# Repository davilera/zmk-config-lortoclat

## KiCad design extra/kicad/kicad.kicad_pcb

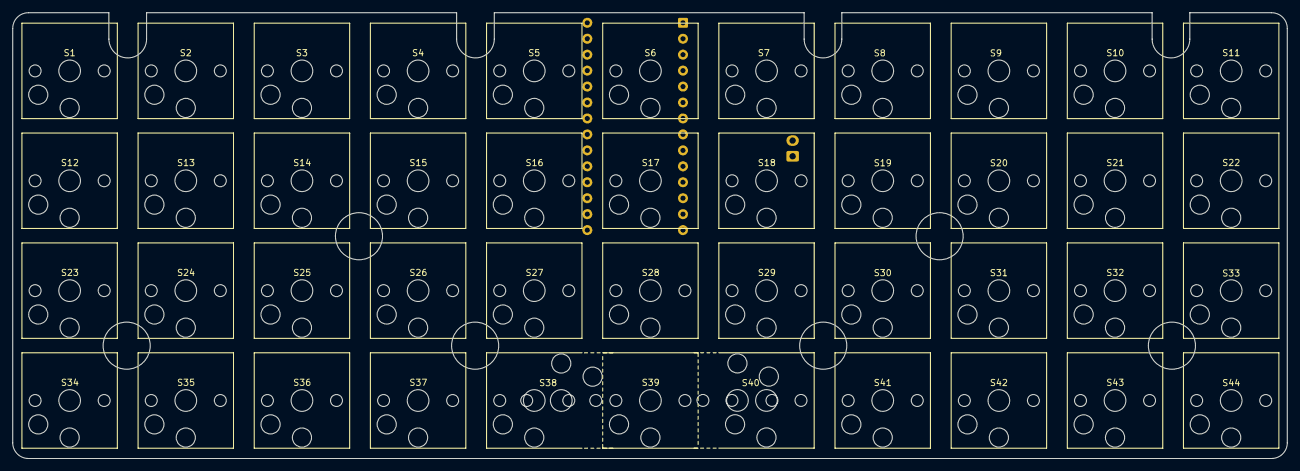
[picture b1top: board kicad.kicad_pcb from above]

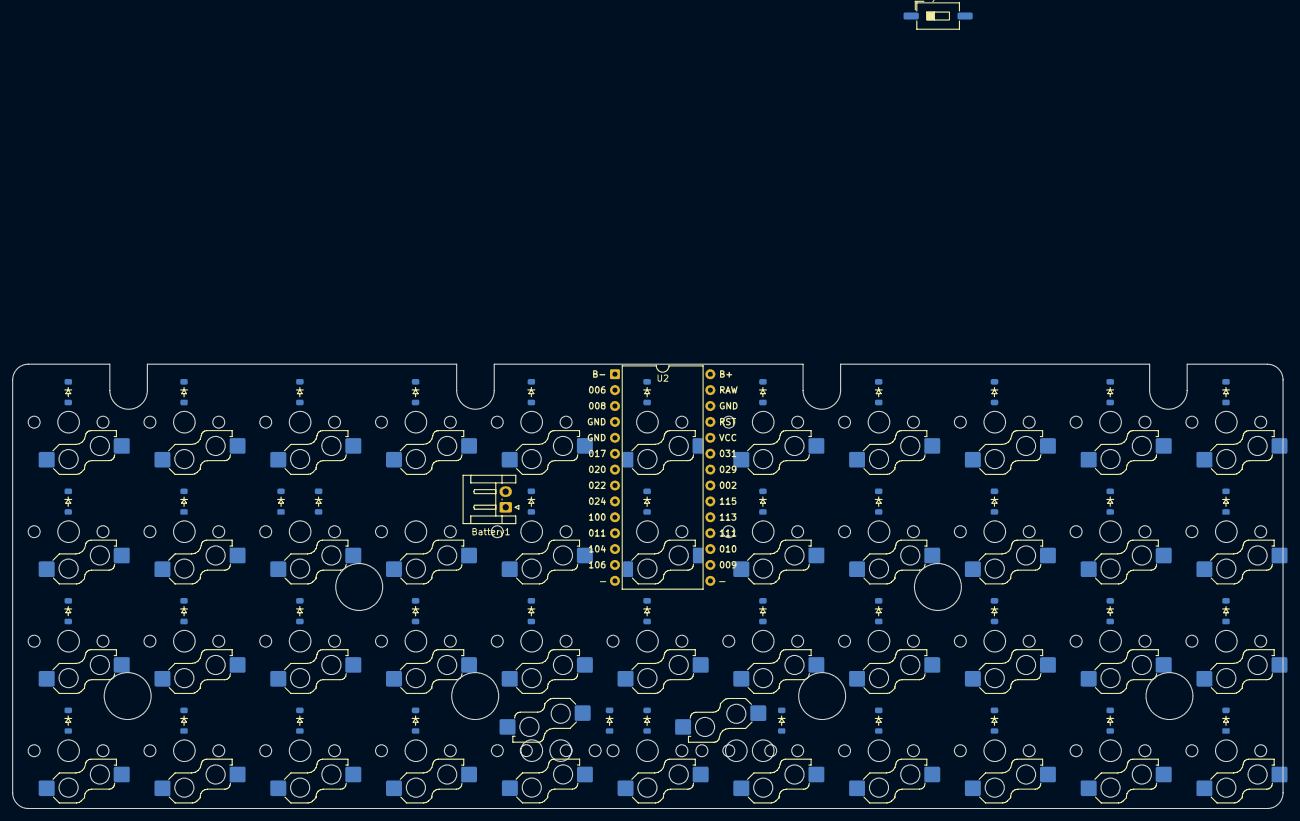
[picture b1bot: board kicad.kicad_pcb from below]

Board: 2 copper layers, 203.0 x 71.0 mm, 93 parts (47 on the bottom side), 62 nets, no tracks yet.

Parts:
Battery1: Battery_Cell; JST_EH_S2B-EH_1x02_P2.50mm_Horizontal
BatterySwitch1: Switch; SW_DIP_SPSTx01_Slide_6.7x4.1mm_W8.61mm_P2.54mm_LowProfile
D1, D2, D3, D4, D5, D6, D7, D8, D9, D10, D11, D12, D13, D14, D15, D16, D17, D18, D19, D20, D21, D22, D23, D24, D25, D26, D27, D28, D29, D30, D31, D32, D33, D34, D35, D36, D37, D38, D39, D40, D41, D42, D43, D44: Diode_SOD-123
S1, S2, S3, S4, S5, S6, S7, S8, S9, S10, S11, S12, S13, S14, S15, S16, S17, S18, S19, S20, S21, S22, S23, S24, S25, S26, S27, S28, S29, S30, S31, S32, S33, S34, S35, S36, S37, S38, S39, S40, S41, S42, S43, S44, S45, S46: Hotswap_Choc_V1
U2: MW-R-DP-W; DIP-28_W15.24mm

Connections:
B+: Battery1.1 (+), U2.28 (VCC)
B-: BatterySwitch1.2, U2.1 (GND), U2.14 (GND)
Column 0: S1.1, S12.1, S23.1, S34.1, U2.22 (ADC1/AI1)
Column 1: S2.1, S13.1, S24.1, S35.1, U2.21 (~RESET)
Column 2: S3.1, S14.1, S25.1, S36.1, U2.20 (DIO17/BPS)
Column 3: S4.1, S15.1, S26.1, S37.1, U2.19 (DIO15/SDA)
Column 4: S5.1, S16.1, S27.1, S38.1, S45.1, U2.18 (DIO16/DI4)
Column 5: S6.1, S17.1, S28.1, S39.1, U2.16 (DIO13/DI2)
Column 6: S7.1, S18.1, S29.1, S40.1, S46.1, U2.13 (DIO10/M1)
Column 7: S8.1, S19.1, S30.1, S41.1, U2.12 (DIO9/DO4)
Column 8: S9.1, S20.1, S31.1, S42.1, U2.11 (DIO8/PWM4)
Column 9: S10.1, S21.1, S32.1, S43.1, U2.10 (DIO6/TX)
Column 10: S11.1, S22.1, S33.1, S44.1, U2.9 (DIO4/DO3)
unnamed: Battery1.2 (-), BatterySwitch1.1
unnamed: D1.2 (A), S1.2
unnamed: D2.2 (A), S2.2
unnamed: D3.2 (A), S3.2
unnamed: D4.2 (A), S4.2
unnamed: D5.2 (A), S5.2
unnamed: D6.2 (A), S6.2
unnamed: D7.2 (A), S7.2
unnamed: D8.2 (A), S8.2
unnamed: D9.2 (A), S9.2
unnamed: D10.2 (A), S10.2
unnamed: D11.2 (A), S11.2
unnamed: D12.2 (A), S12.2
unnamed: D13.2 (A), S13.2
unnamed: D14.2 (A), S14.2
unnamed: D15.2 (A), S15.2
unnamed: D16.2 (A), S16.2
unnamed: D17.2 (A), S17.2
unnamed: D18.2 (A), S18.2
unnamed: D19.2 (A), S19.2
unnamed: D20.2 (A), S20.2
unnamed: D21.2 (A), S21.2
unnamed: D22.2 (A), S22.2
unnamed: D23.2 (A), S23.2
unnamed: D24.2 (A), S24.2
unnamed: D25.2 (A), S25.2
unnamed: D26.2 (A), S26.2
unnamed: D27.2 (A), S27.2
unnamed: D28.2 (A), S28.2
unnamed: D29.2 (A), S29.2
unnamed: D30.2 (A), S30.2
unnamed: D31.2 (A), S31.2
unnamed: D32.2 (A), S32.2
unnamed: D33.2 (A), S33.2
unnamed: D34.2 (A), S34.2
unnamed: D35.2 (A), S35.2
unnamed: D36.2 (A), S36.2
unnamed: D37.2 (A), S37.2
unnamed: D38.2 (A), S38.2, S45.2
unnamed: D39.2 (A), S39.2
unnamed: D40.2 (A), S40.2, S46.2
unnamed: D41.2 (A), S41.2
unnamed: D42.2 (A), S42.2
unnamed: D43.2 (A), S43.2
unnamed: D44.2 (A), S44.2
Row 0: D1.1 (K), D2.1 (K), D3.1 (K), D4.1 (K), D5.1 (K), D6.1 (K), D7.1 (K), D8.1 (K), D9.1 (K), D10.1 (K), D11.1 (K), U2.2 (DIO14/SCL)
Row 1: D12.1 (K), D13.1 (K), D14.1 (K), D15.1 (K), D16.1 (K), D17.1 (K), D18.1 (K), D19.1 (K), D20.1 (K), D21.1 (K), D22.1 (K), U2.3 (DIO7/RX)
Row 2: D23.1 (K), D24.1 (K), D25.1 (K), D26.1 (K), D27.1 (K), D28.1 (K), D29.1 (K), D30.1 (K), D31.1 (K), D32.1 (K), D33.1 (K), U2.6 (DO0/PWM2)
Row 3: D34.1 (K), D35.1 (K), D36.1 (K), D37.1 (K), D38.1 (K), D39.1 (K), D40.1 (K), D41.1 (K), D42.1 (K), D43.1 (K), D44.1 (K), U2.7 (DO1/PWM3)

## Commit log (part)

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2024-08-25 Initial User Config.
2024-08-25 Rename files
2024-08-25 Add shield
2024-08-25 Use proper files in shield
2024-08-25 Import keymap from Ben Vallack
2024-08-29 Format overlay
2024-09-01 Add empty readme file
2024-09-01 Add Shell 3D model(s)
2024-09-01 Add Lid 3D model(s)
2024-09-01 Remove Blender backup file
2024-09-01 Add Cover 3D model(s)
2024-09-10 Add Hood 3D model(s)
2024-09-10 Improve Shell 3D model(s)
2024-09-12 Add PCB 3D model(s)
2024-09-18 Update Cover 3D model(s)
2024-09-18 Update pins
2024-09-18 Add test layer
2024-09-18 Fix test layer
2024-09-18 Remove test layer
2024-09-19 Enable BT
2024-09-19 Fix a few names
2024-09-19 Testing BT and thumbs
2024-09-19 Fix layer switch
2024-09-23 Update models to use horizontal thumb keys
2024-09-23 --amend
2024-09-25 Fix cover model
2024-09-25 Test hold-tap
2024-09-25 Fix layers
2024-09-25 Add hold-tap
2024-09-25 Remove unicode and use modifier instead
2024-09-26 Test i18n characters with macros
2024-09-26 Add missing colons
2024-09-26 Fix macro
2024-09-26 Remove invalid include
2024-09-26 Fix typo
2024-09-26 Fix macro definition
2024-09-26 Tweak macro
2024-09-26 Tweak hold tap to accept macro
2024-09-26 Tweak macro speed
2024-09-27 Extract macros into their own file
2024-09-27 Add multiple macros
2024-09-27 Add missing key
2024-09-27 Fixing macros
2024-09-27 Try to fix macros
2024-09-27 Undo macros
2024-09-27 Add macros
2024-09-27 Fix macro name
2024-09-27 Fix two macros
2024-09-29 Define layouts
2024-09-29 Remove invalid keycode
2024-09-29 Fix shift code
2024-09-29 Remove all layers to find error
2024-09-29 Add i18n
2024-09-29 Add sym1
2024-09-29 Add sym2
2024-09-29 Add sys
2024-09-29 Add num
2024-09-29 Add BT
2024-09-29 Use appropriate event for BT codes
2024-09-29 Fix BT
2024-09-29 Swap two keys
2024-09-29 Change space to send dot on double-tap
2024-09-29 Reverse behavior
2024-09-29 Tweak tapping term in space
2024-09-29 Add num/rpt key
2024-09-29 Fix num/rpt key
2024-09-29 Add more i18n chars
2024-09-29 Complete i18n layer
2024-09-30 Add ß
2024-09-30 Add more keys
2024-09-30 Fix duplicated name
2024-09-30 Duplicate sym layer
2024-09-30 Debug layers
2024-09-30 Enable i18n layer
2024-09-30 Enable sym1 layer
2024-09-30 Enable sym2 layer
2024-09-30 Fix sym2 layer
2024-09-30 Enable sys layer
2024-09-30 Fix num layer
2024-09-30 Enable BT layer
2024-09-30 Fix shift in i18n
2024-10-01 Fix guillemots
2024-10-01 Swap CTRL and ALT keys plus minor improvements
2024-10-01 Relocate some combos to alpha 1
2024-10-01 Swap two num keys
2024-10-01 Use numpad numbers in num layer
2024-10-02 Tweak a few keys
2024-10-09 Make alpha2 and i18n layers sticky
2024-10-09 Tweak sticky key behavior
2024-10-09 Tweak sl instead of sk behavior
2024-10-25 Remap a few keys
2024-10-25 Improve hold tap
2024-10-25 Improve hold tap in right thumbs
2024-10-28 Fix duplicate node name
2024-10-29 Move a few more keys around
2024-10-30 Fix a few keys
2024-11-02 Rename keyboard
2024-11-02 Add KLE json file
2024-11-02 Fix KLE JSON
2024-11-02 Fix keyboard JSON
2024-11-02 Remove key
2024-11-02 Simplify layout
2024-11-02 Fix typos and bugs
2024-11-02 Fix wide key position
2024-11-02 Fix JSON
2024-11-02 Fix keymap
2024-11-02 Add layers
2024-11-02 Set all keys in all secondary layers to none
2024-11-02 Add missing keys in alpha layer
2024-11-02 Add layer switches and a few more keys
2024-11-02 Add i18n keys without macros
2024-11-02 Add missing i18n keys
2024-11-03 Add test macro
2024-11-03 Add i18n macros into i18n layer
2024-11-03 Add sym layer
2024-11-03 Add num layer
2024-11-03 Add sys layer
2024-11-24 Add keyboard model
2024-11-26 Fix models
2024-12-19 Update 3d models
2024-12-23 Update config files
2024-12-23 Update JSON
2024-12-23 Add missing keys in keymap
2024-12-23 Test layout
2024-12-28 Fix some i18n keys
2024-12-28 Tweak more keys
2024-12-28 Tweak fn keys
2024-12-29 Add MO keys
2024-12-29 Add "I" macros
2024-12-29 Tweak shift/caps behavior
2024-12-30 Add qwerty
2024-12-30 Reorder mod keys
2024-12-30 Add symbol tweak on qwerty
2024-12-30 Tweak conditional layers
2024-12-30 Add access to num layer
2024-12-30 Add ctrl nums
2024-12-31 Add shifts as modtaps
2024-12-31 Fix keys in qwerty i18n
2024-12-31 Change mod row
2024-12-31 Add number row as hold keys
2024-12-31 Fix shift
2024-12-31 Add num row in qwerty
2024-12-31 Tweak combo
2025-01-03 Fix qwerty num layout
2025-01-08 Swap LALT and LGUI keys
2025-01-09 Move sym keys one position outwards
2025-01-09 Tweak arrows in sym layer
2025-01-10 Swap M and D
2025-01-10 Move some keys around
2025-01-10 Add ndash and mdash characters
2025-01-10 Remap bottom row again
2025-01-10 Remap some symbols
2025-01-10 Add missing macros
2025-01-14 Trying out new mods
2025-01-15 Remap a ton of keys in multiple layers
2025-01-15 Tweak layer reset in num layer
2025-01-15 Add del key and some more tweaks
2025-01-15 Add page up/down buttons
2025-01-16 Tweak symbols again
2025-01-16 Swap two more syms for comfort
2025-01-17 Add home row mods in isrt
2025-01-17 Access symbols via home row mods only
2025-01-17 Tweak shift hrm
2025-01-17 Tweak shift location again
2025-01-22 Add more homerow mods and tweak some thumb keys
2025-01-22 Fix TD key
2025-01-23 Add shift in FN layer
2025-01-23 Add missing models
2025-01-23 Switch to just qwerty
2025-01-23 Tweak last key to caps/num
2025-01-23 Remap all symbols to better match QWERTY layout
2025-01-23 Remove unnecessary keys
2025-01-30 Tweak braces and brackets
2025-01-30 Tweak access to num layer
2025-01-30 Add extra keys in sym layer
2025-02-04 Add LT behavior on right thumb key
2025-02-13 Make enter and esc always available
2025-02-13 Fix open question mark in i18n layer
2025-02-24 Workaround to fix non-working key
2025-02-25 Remap tab to same key
2025-02-25 Tweak right thumb space on sym
2025-03-27 Tweak some keys
2025-05-19 Fix fn and add gaming layer
2025-05-19 Remove duplicate
2025-05-20 Remap layer switchers
2025-05-22 Revert keys
2025-05-27 back from numeric to programming
2025-05-27 Add FN to numeric layer
2025-07-04 Move i18n quotes around
2025-07-05 Fix central key
2025-07-05 Swap tab and enter keys
2025-07-05 Swap tab and enter again
2025-07-07 Clean alphas
2025-07-08 Restore tab in FN
2025-07-09 Add repeat key
2025-07-09 Add behavior to implement repeat key on hold
2025-07-09 Use repeat in central key
2025-07-18 Add F5, F12 and POWER keys
2025-07-23 Add some shortcuts to FN layer
2025-07-23 Tweak combos
2025-07-23 Fix access to FN from NUM
2025-07-23 Tweak num layer
2025-07-23 Add kitty shortcuts
2025-07-29 Add Fkeys layer
2025-07-29 Add mo layers in FN layer equivalent to combos
2025-07-30 Allow slow combos
2025-07-30 Remove CTRL from HRM
2025-07-30 Clean layers
2025-07-30 Updated lortoclat.keymap
2025-07-31 Add TAB in center
2025-08-06 Remap power button
2025-10-02 Remap enter to center
2025-10-02 Switch tab and enter
2025-10-02 Tweak num keys
2025-10-03 Disable enter key in FN layer until I get used to it not being tab anymore
2025-11-10 Add capital grave vowels using combos
2025-11-10 Fix macro typo
2025-11-10 Remove weird macros
2025-11-10 Improve access to num layer
2025-11-11 Tweak numpad
2025-12-16 Add more arrows in FN to use keyboard with one hand
2025-12-23 Fix board
2026-01-21 Fix keys
2026-01-21 Add i18n caps
2026-02-09 Implement tap dance on Q key to test possible behavior
2026-02-09 Tweak term
2026-02-09 Reverse behaviors
2026-02-09 Tweak hkp behavior to allow double-tap to send multiple letters
2026-02-09 Increase delay for repeating key in tap-hold
2026-02-09 Replicate hold/tap behavior in home row
2026-02-20 Tweak combos and num layer
2026-02-20 Fix combo
2026-06-08 Access num layer from home row
2026-06-10 Fix nice nano v2 board configuration
2026-06-10 Add more mods in main and bottom rows
2026-06-10 Fix apps layer
2026-06-10 Remove numbers from top row
2026-06-10 Fix apps
2026-06-10 Rename key
2026-06-10 Add dollar to numpad
2026-06-10 Add tab navigation to numpad layer
2026-06-15 Remap zero and dot
2026-06-15 Add some useful keys in numpad
2026-06-16 Add N0 to sym
2026-06-29 Tweak numpad layer
